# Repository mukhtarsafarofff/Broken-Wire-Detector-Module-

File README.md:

(ENG) Portable loads such as video cameras, halogen flood lights, electrical irons, hand drillers, grinders, and cutters are powered by connecting long 2- or 3-core cables to the mains plug. Due to prolonged usage, the power cord wires are subjected to mechanical strain and stress, which can lead to internal snapping of wires at any point. In such a case most people go for replacing the core/cable, as finding the exact location of a broken wire is difficult. The circuit presented here can easily and quickly detect a broken/faulty wire and its breakage point in 1-core, 2-core, and 3-core cables without physically disturbing wires and this circuit is built using CD4069 Hex inverter.Gates N3 and N4 are used as a pulse generator that oscillates at around 1000 Hz in audio range.  The frequency is determined by timing components comprising resistors R3 and R4, and capacitor C1. Gates N1 and N2 are used to sense the presence of 230V AC field around the live wire and buffer weak AC voltage picked from the test probe. The voltage at output pin 10 of gate N2 can enable or inhibit the oscillator circuit. When the test probe is away from any high-voltage AC field, output pin 10 of gate N2 remains low. As a result, diode D3 conducts and inhibits the oscillator circuit from oscillating. Simultaneously, the output of gate N3 at pin 6 goes ‘low’ to cut off transistor T1. As a result, LED1 goes off. When the test probe is moved closer to 230V AC, 50Hz mains live wire, during every positive half-cycle, output pin 10 of gate N2 goes high.  A 3V DC supply is sufficient for powering the whole circuit. Alternatively, one may use two 1.5V R6- or AA-type batteries. Using this gadget, one can also quickly detect fused small filament bulbs in serial loops powered by 230V AC mains. 
 Then connect 230V AC mains live wire at one end of the faulty wire, leaving the other end free. Connect neutral terminal of the mains AC to the remaining wires at one end. However, if any of the remaining wires is also found to be faulty, then both ends of these wires are connected to neutral. For single-wire testing, connecting neutral only to the live wire at one end is sufficient to detect the breakage point. To detect the breakage point, turn on switch S1 and slowly move the test probe closer to the faulty wire, beginning with the input point of the live wire and proceeding towards its other end. LED1 starts glowing during the presence of AC voltage in faulty wire. When the breakage point is reached, LED1 immediately extinguishes due to the non-availability of mains AC voltage. During testing avoid any strong electric field close to the circuit to avoid false detection.

(DEU) Tragbare Lasten wie Videokameras, Halogenfluter, elektrische Bügeleisen, Handbohrer, Schleifmaschinen und Schneidgeräte werden durch das Anschließen langer 2- oder 3-adriger Kabel an den Netzstecker mit Strom versorgt. Durch den langanhaltenden Gebrauch werden die Drähte des Stromkabels mechanisch beansprucht, was zu einem internen Bruch der Drähte an beliebigen Stellen führen kann. In einem solchen Fall entscheiden sich die meisten Menschen dafür, den Kern/das Kabel zu ersetzen, da das Auffinden der genauen Bruchstelle eines Drahtes schwierig ist. Die hier vorgestellte Schaltung kann schnell und einfach einen gebrochenen/fehlerhaften Draht sowie dessen Bruchstelle in 1-, 2- und 3-adrigem Kabel erkennen, ohne die Drähte physisch zu stören, und diese Schaltung wird mit einem CD4069 Hex-Inverter gebaut. Die Tore N3 und N4 werden als Impulsgenerator verwendet, der mit etwa 1000 Hz im Audio-Bereich schwingt. Die Frequenz wird durch die Timing-Komponenten, bestehend aus den Widerständen R3 und R4 sowie dem Kondensator C1, bestimmt. Die Tore N1 und N2 dienen dazu, das Vorhandensein eines 230V Wechselstromfeldes um den stromführenden Draht zu erkennen und eine schwache Wechselspannung, die von der Prüfsonde aufgenommen wird, zu puffern. Die Spannung am Ausgangspin 10 von Tor N2 kann den Oszillatorschaltkreis aktivieren oder deaktivieren. Wenn die Prüfsonde von einem Hochspannungs-Wechselstromfeld entfernt ist, bleibt der Ausgangspin 10 von Tor N2 niedrig. Infolgedessen leitet die Diode D3 und verhindert, dass der Oszillatorkreis schwingt. Gleichzeitig wird der Ausgang von Tor N3 an Pin 6 ‚niedrig‘, um den Transistor T1 abzuschalten. Infolgedessen erlischt LED1. Wenn die Prüfsonde näher an den 230V AC, 50Hz, stromführenden Hauptdraht bewegt wird, geht während jedes positiven Halbzyklus der Ausgangspin 10 von Tor N2 hoch. Eine 3V DC-Stromversorgung reicht aus, um den gesamten Schaltkreis zu versorgen. Alternativ kann man auch zwei 1,5V R6- oder AA-Batterien verwenden. Mit diesem Gerät kann man auch schnell durchgebrannte kleine Glühbirnen in Serienschaltungen, die von 230V Wechselstrom gespeist werden, erkennen. Dann schließen Sie den 230V Wechselstrom-Hauptdraht an einem Ende des fehlerhaften Drahtes an und lassen das andere Ende frei. Verbinden Sie den Neutralleiter des Wechselstroms mit den verbleibenden Drähten an einem Ende.  Wenn jedoch einer der verbleibenden Drähte ebenfalls fehlerhaft ist, dann werden beide Enden dieser Drähte mit Neutral verbunden.  Für Einzeldrahttests reicht es aus, Neutral nur an das stromführende Ende anzuschließen, um den Bruchpunkt zu erkennen . Um den Bruchpunkt zu erkennen, schalten Sie den Schalter S1 ein und bewegen Sie die Prüfsonde langsam näher an den fehlerhaften Draht, beginnend beim Eingangspunkt des stromführenden Drahtes und fortschreitend zu dessen anderem Ende. LED1 beginnt zu leuchten während der Anwesenheit von Wechselspannung im fehlerhaften Draht. Wenn der Bruchpunkt erreicht ist, erlischt LED1 sofort aufgrund der Nichtverfügbarkeit der Wechselstrom-Hauptspannung. Während des Tests vermeiden Sie jedes starke elektrische Feld in der Nähe des Schaltkreises, um Fehldetektionen zu vermeiden.

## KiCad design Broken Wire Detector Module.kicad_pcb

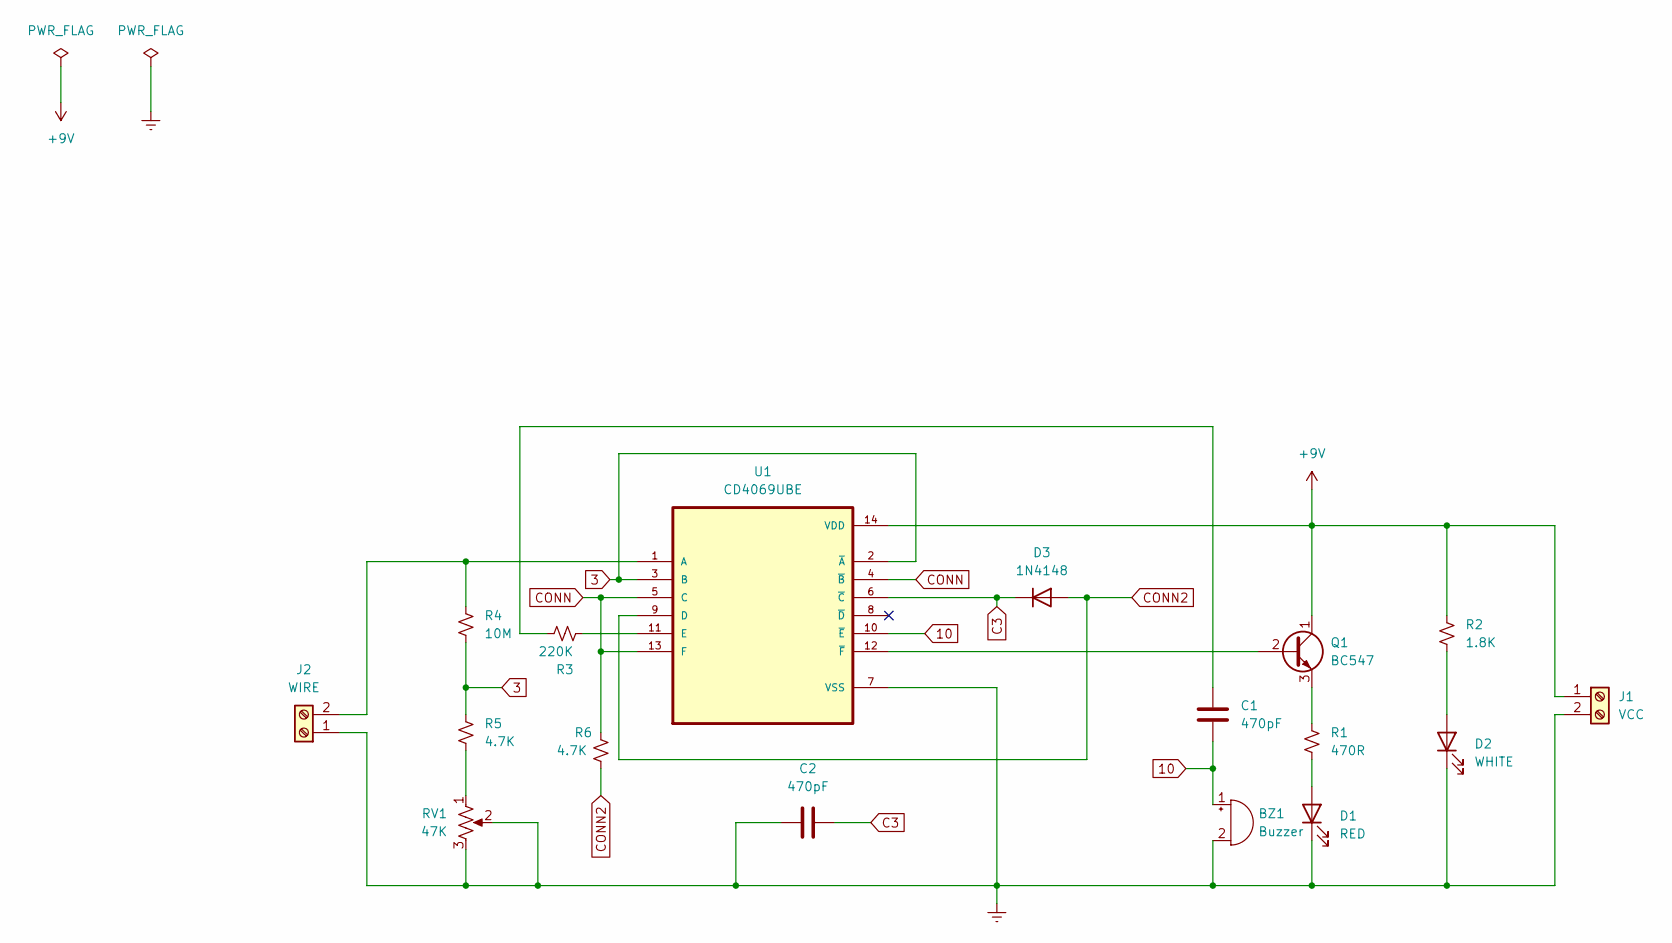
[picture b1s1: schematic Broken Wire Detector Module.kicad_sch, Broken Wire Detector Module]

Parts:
BZ1: Buzzer; Buzzer_12x9.5RM7.6
C1, C2: 470pF; C_Disc_D8.0mm_W5.0mm_P7.50mm
D1: RED; LED_D5.0mm
D2: WHITE; LED_D5.0mm_Clear
D3: 1N4148; D_DO-35_SOD27_P7.62mm_Horizontal
J1: VCC; TerminalBlock_bornier-2_P5.08mm
J2: WIRE; TerminalBlock_bornier-2_P5.08mm
Q1: BC547; TO-92_Inline
R1: 470R; R_Axial_DIN0309_L9.0mm_D3.2mm_P12.70mm_Horizontal
R2: 1.8K; R_Axial_DIN0309_L9.0mm_D3.2mm_P12.70mm_Horizontal
R3: 220K; R_Axial_DIN0309_L9.0mm_D3.2mm_P12.70mm_Horizontal
R4: 10M; R_Axial_DIN0309_L9.0mm_D3.2mm_P12.70mm_Horizontal
R5, R6: 4.7K; R_Axial_DIN0309_L9.0mm_D3.2mm_P12.70mm_Horizontal
RV1: 47K; Potentiometer_Vishay_148-149_Single_Horizontal
U1: CD4069UBE; DIP-14_W7.62mm

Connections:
3: R4.2, R5.1, U1.2 (~A), U1.3 (B)
10: BZ1.1 (-), C1.1, U1.10 (~E)
+9V: J1.1, Q1.1 (C), R2.1, U1.14 (VDD)
C3: C2.1, D3.1 (K), U1.6 (~C)
CONN: R6.1, U1.4 (~B), U1.5 (C), U1.13 (F)
CONN2: D3.2 (A), R6.2, U1.9 (D)
Earth: BZ1.2 (+), C2.2, D1.1 (K), D2.1 (K), J1.2, J2.1, RV1.2, RV1.3, U1.7 (VSS)
unnamed: C1.2, R3.2
unnamed: D1.2 (A), R1.2
unnamed: D2.2 (A), R2.2
unnamed: J2.2, R4.1, U1.1 (A)
unnamed: Q1.2 (B), U1.12 (~F)
unnamed: Q1.3 (E), R1.1
unnamed: R5.2, RV1.1
unnamed: R3.1, U1.11 (E)

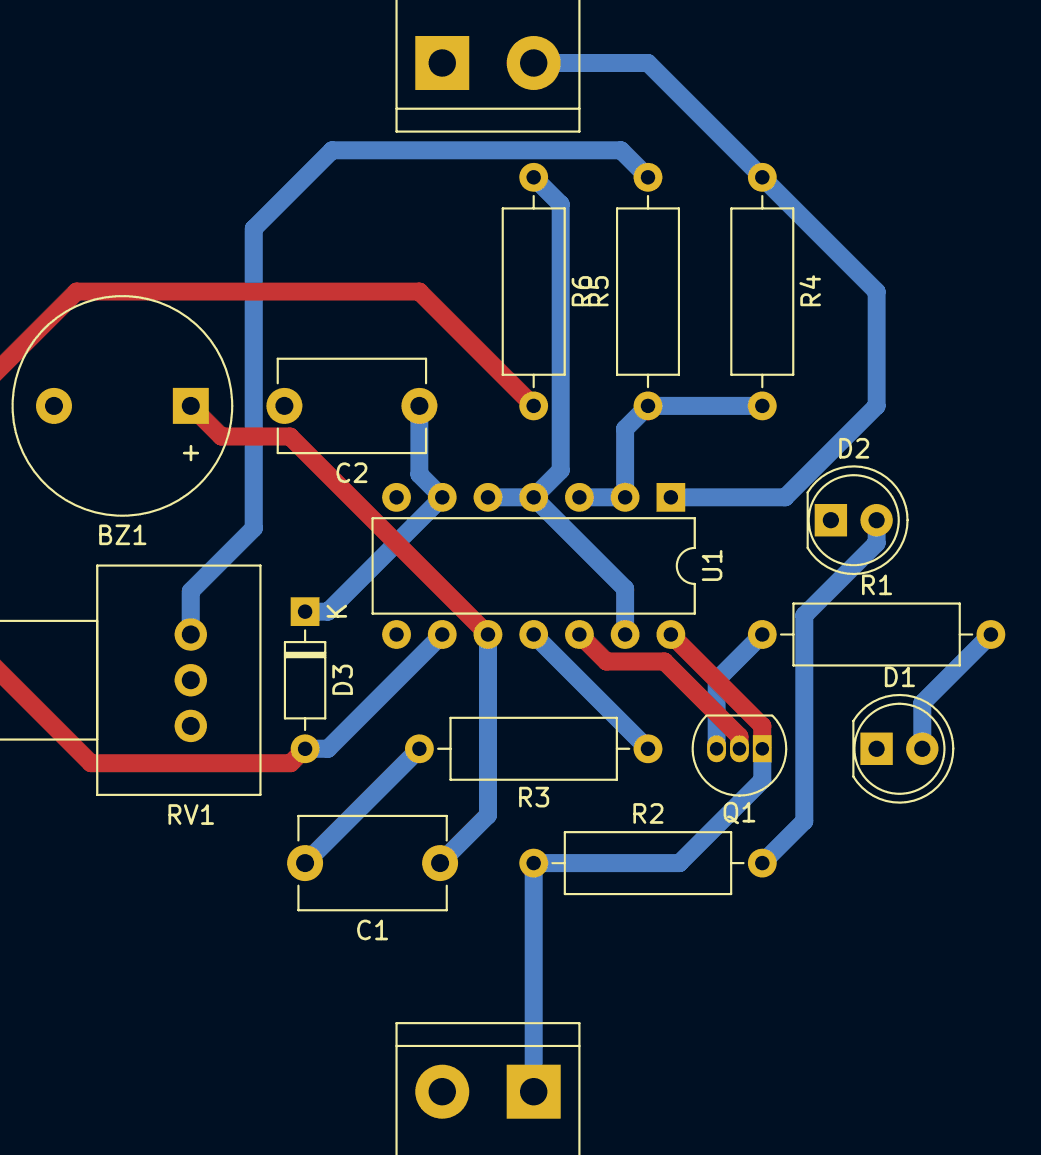
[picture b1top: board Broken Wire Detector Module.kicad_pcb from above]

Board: 2 copper layers, 17 parts (0 on the bottom side), 15 nets.

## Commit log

2024-04-05 Broken Wire Detector Module is accomplished
2024-04-05 Update README.md\
